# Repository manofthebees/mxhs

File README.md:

# mxhs
simple hotswap single switch pcb for handwired keyboards

## picture

## BOM
- mx hotswap sockets
- SOD 123 1n4148 diodes

## Prototype PCBS sponsored by [PCBway](https://www.pcbway.com/)!

upload the grbr from the releases tab & select "panel by pcbway" & then enter 4*5.
this will give you 100 pcbs :)

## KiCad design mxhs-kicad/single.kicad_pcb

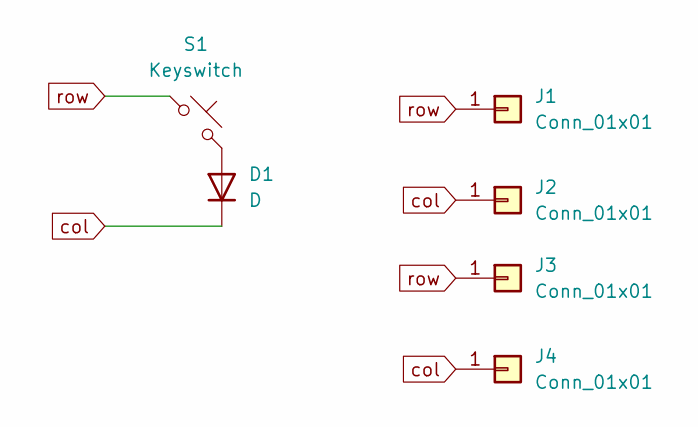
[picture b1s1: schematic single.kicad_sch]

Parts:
D1: D; Diode_SOD-123
J1, J2, J3, J4: Conn_01x01; TestPoint_Pad_1.5x1.5mm
S1: Keyswitch; MX_Hotswap_1.00u

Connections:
unnamed: D1.2 (A), S1.2
col: D1.1 (K), J2.1, J4.1
row: J1.1, J3.1, S1.1

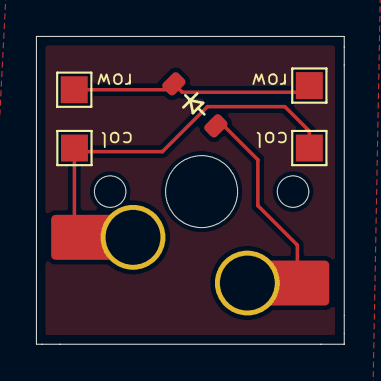
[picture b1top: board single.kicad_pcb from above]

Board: 2 copper layers, 17.1 x 17.1 mm, 6 parts (0 on the bottom side), 3 nets.

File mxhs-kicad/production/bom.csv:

Designator,Footprint,Quantity,Value,LCSC Part #
D1,Diode_SOD-123,1,D,
"J1, J2, J3, J4",TestPoint_Pad_1.5x1.5mm,4,Conn_01x01,
S1,MX_Hotswap_1.00u,1,Keyswitch,

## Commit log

2025-01-13 add pcb
2025-01-13 add images
2025-01-13 fix image & fix write up
2025-01-13 adjust picture
2025-01-13 ignore prod & backups
2025-01-24 increase sizing to fit behind a cutout
2025-01-24 add pcbway sponsor to readme
2025-01-24 add img
